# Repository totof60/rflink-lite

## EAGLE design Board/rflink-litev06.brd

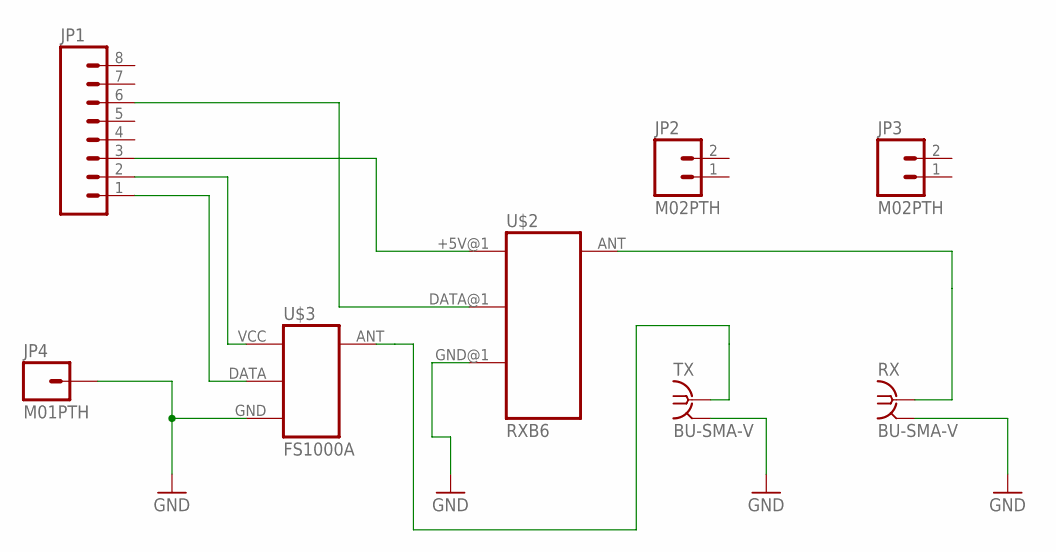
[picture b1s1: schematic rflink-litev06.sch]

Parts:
JP1: M081X08; 1X08
JP2, JP3: M02PTH; 1X02
JP4: M01PTH; 1X01
RX: BU-SMA-V
TX: BU-SMA-V
U$2: RXB6; RF-LINK_RX
U$3: FS1000A; RF-LINK_TX

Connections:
GND: JP4.1, RX.2, RX.3 (2), RX.4 (2), RX.5 (2), TX.2, TX.3 (2), TX.4 (2), TX.5 (2), U$2.GND@1 (GND), U$3.GND
unnamed: TX.1, U$3.ANT
unnamed: RX.1, U$2.ANT
unnamed: JP1.1, U$3.DATA
unnamed: JP1.3, U$2.+5V@1 (+5V)
unnamed: JP1.6, U$2.DATA@1 (DATA)
unnamed: JP1.2, U$3.VCC (+5V)

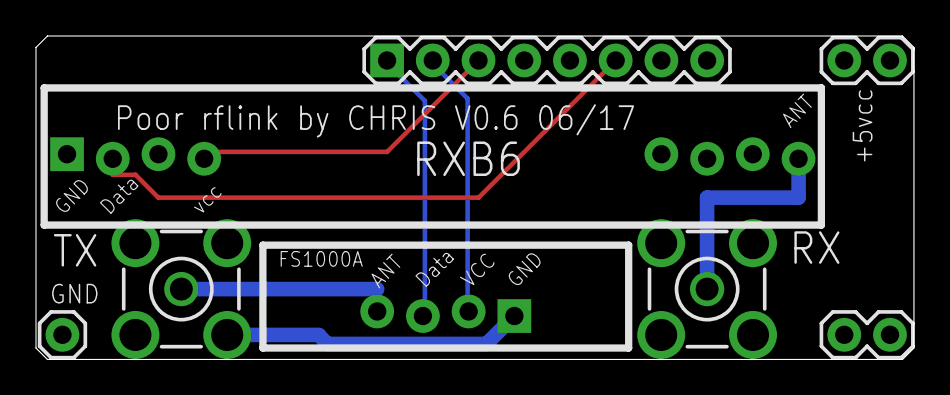
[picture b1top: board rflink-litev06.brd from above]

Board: 2 copper layers, 48.8 x 18.0 mm, 8 parts (0 on the bottom side), 7 nets.

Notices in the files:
parts and their libraries:
SparkFun-Connectors: Licensing: CC v3.0 Share-Alike You are welcome to use this library for commercial purposes.
